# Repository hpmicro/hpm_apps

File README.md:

[中文](README_zh.md)

# HPM APPS introduction
HPM APPS is an upper layer application software development kit based on HPM SDK. It provides a variety of typical general-purpose application solutions, including middleware, components, services, etc., for users to use and evaluate.

## HPM APPS directory structure

| Directory name | Description |
|--------|--------|
| <HPM_APP_BASE>/boards | Files for various development boards |
| <HPM_APP_BASE>/components | Software components |
| <HPM_APP_BASE>/docs | Document |
| <HPM_APP_BASE>/middleware | Middleware |
| <HPM_APP_BASE>/apps | Samples of various solutions |
| <HPM_APP_BASE>/services | Software Services |
| <HPM_APP_BASE>/tools | Tool files |

## Instructions for using the HPM APP

### HPM SDK version requirements

Note: Each CASE of the HPM APP relies on the corresponding HPM SDK version. To ensure that the project can be built and compiled correctly, please refer to the SDK version dependency instructions in the README document located in the corresponding CASE directory.

### Build

Recommend using the sdk_env environment on Windows to build the SES compilation and debugging project. In the SDK ENV tool, check **Enable User Application Path** and select the **hpm_apps/apps** directory, or choose the demo directory you need. It is recommended to use the former, as it can scan all demo files.

If you want to add some middleware from hpm_apps/middleware, please add code in demo CMakeLists.txt, suggest you add code before `generate_ses_project`, for example:

```
add_subdirectory(../../.. hpm_apps/build_tmp)
generate_ses_project()
```

## HPM_APPS documentation

- Local document:
  The HPM_APPS document can be compiled locally, and after successful compilation, the local document can be accessed through the following portals:
  - <HPM_APP_BASE>>/docs/index.html
  - <HPM_APP_BASE>>/docs/index_zh.html

- Online documentation:
  - https://hpm-apps.readthedocs.io/en/latest/
  - https://hpm-apps.readthedocs.io/zh-cn/latest/

## Code repository
- hpm_apps github: https://github.com/hpmicro/hpm_apps
- hpm_sdk github: https://github.com/hpmicro/hpm_sdk
- sdk_env github: https://github.com/hpmicro/sdk_env
- sdk extra demo: https://github.com/hpmicro/hpm_sdk_extra
- openocd (hpmicro patched): https://github.com/hpmicro/riscv-openocd
- gnu gcc toolchain: https://github.com/hpmicro/riscv-gnu-toolchain

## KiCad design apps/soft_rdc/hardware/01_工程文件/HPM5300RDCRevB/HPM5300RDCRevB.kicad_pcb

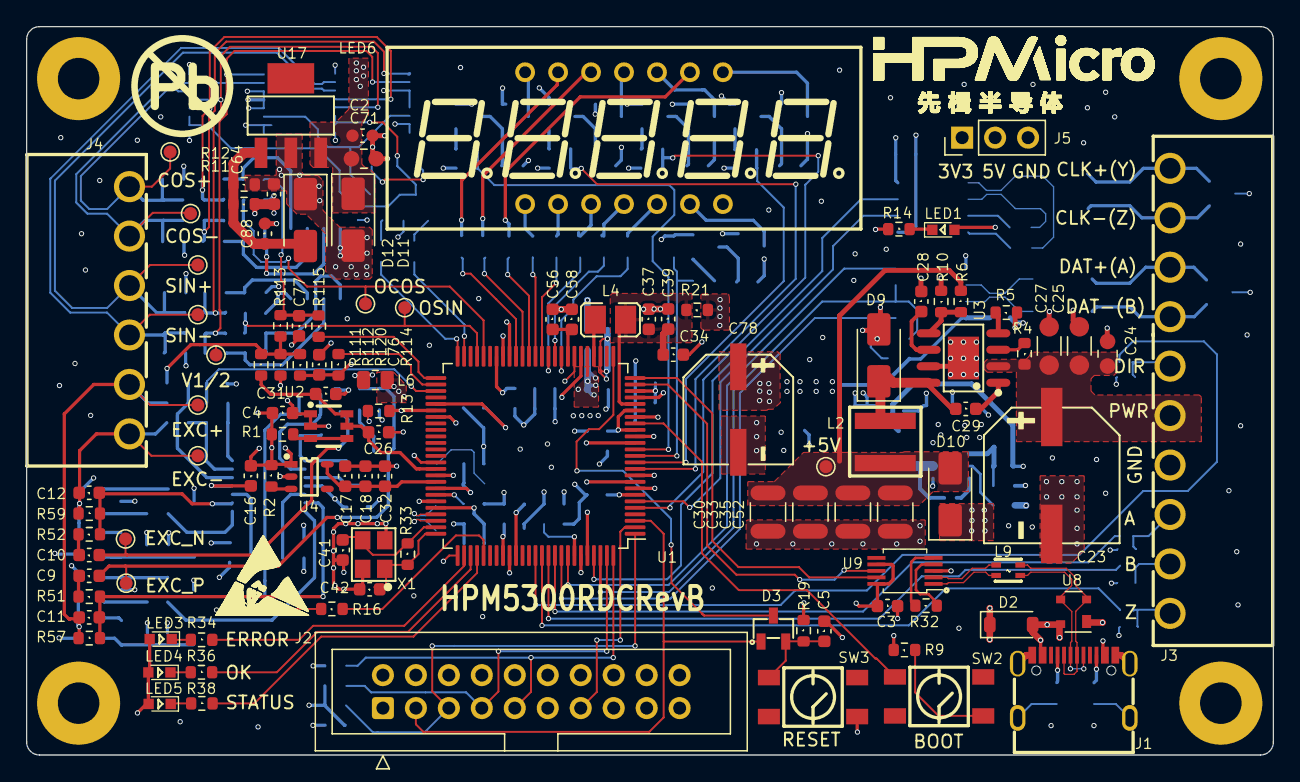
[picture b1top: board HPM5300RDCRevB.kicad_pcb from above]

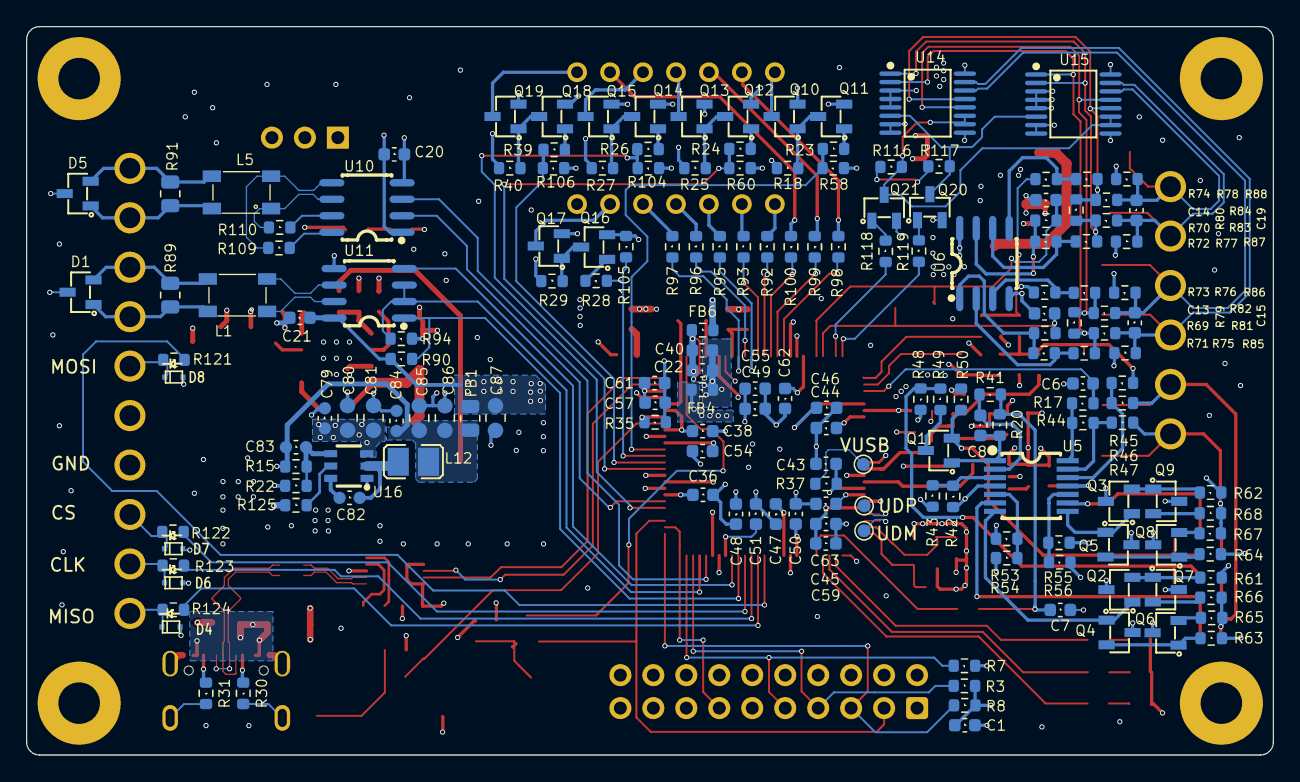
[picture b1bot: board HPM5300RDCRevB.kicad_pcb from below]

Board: 4 copper layers, 96.1 x 56.1 mm, 286 parts (173 on the bottom side), 181 nets.

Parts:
C1, C2, C3, C4, C5, C17, C20, C21, C22, C29, C31, C34, C36, C38, C43, C44, C45, C46, C47, C48, C49, C50, C51, C54, C56, C57, C58, C62, C63, C79, C82, C84: 0.1uF,50V; C_0603_1608Metric
C6, C13, C14: 15pF,50V; C_0603_1608Metric
C7: 4.7nF,50V; C_0603_1608Metric
C8: 1nF,50V; C_0603_1608Metric
C9, C10, C32, C76, C77: 10nF,50V; C_0603_1608Metric
C11, C12: 18pF,50V; C_0603_1608Metric
C15, C19: 1uF,50V; C_0603_1608Metric
C16, C18, C26, C88: 10uF,16V; C_0603_1608Metric
C23: 220uF,50V; CAP-SMD_BD10.0-L10.3-W10.3-FD
C24: 100pF; C_0805_2012Metric
C25, C27: 2.2uF,100V; C_1206_3216Metric
C28: 22nF,50V; C_0603_1608Metric
C30, C33, C35, C52: 47uF,16V,X7R; C_1210_3225Metric
C37, C39, C40: 22uF,10V; C_0603_1608Metric
C41, C42: 12pF,50V; C_0603_1608Metric
C55, C59: 10uF,10V; C_0603_1608Metric
C61: 4.7uF,16V; C_0603_1608Metric
C64: 1uF,25V; C_0603_1608Metric
C71, C80, C81, C85, C86, C87: 22uF,16V; C_0805_2012Metric
C78: 220uF,35V; CAP-SMD_BD8.0-L8.3-W8.3-LS9.1-FD
C83: 22pF,50V; C_0603_1608Metric
D1, D5: NUP2105L; SOT-23
D2: 1N5819HW-7-F; D_SOD-123
D3: BAT54A-7-F; SOT-23
D4, D6, D7, D8: D1213A-01T-7; SOD_523_1P4
D9, D10: SS1045; D_SMA
D11, D12: 1N4002; D_SMA
FB1: 100Ω@100MHz_2A; R_0805_2012Metric
FB4, FB6: 600Ω@100MHz_1.3A; R_0603_1608Metric
FID1, FID2, FID3, FID4: MountingHole_Pad; MountingHole_3.2mm_M3_Pad
J1: USB_Type-C; TYPE-C-16P
J2: 2.54-2*10P简牛; IDC-Header_2x10_P2.54mm
J3: Conn_01x10; CONN-TH_10P-P3.81_KF2EDGR-3.81-10P
J4: Conn_01x06; CONN-TH_6P-P3.81_KF2EDGR-3.81-6P
J5: Conn_01x03; PinHeader_1x03_P2.54mm_Vertical
L1, L5: ACT45B-510-2P-TL003; L4532
L2: 8.2uH_6.1A; IND-SMD_L5.5-W5.3_FEXL0520A-1R0M
L4, L12: 4.7uH_1.4A; L1008
L6: BLM21AG121SN1D; R_0805_2012Metric
L9: DLW21SN900SQ2L; L2012
LED1, LED4: LED_GREEN; LED_0603
LED3: LED_RED; LED_0603
LED5: LED_BLUE; LED_0603
LED6: SLR0365CRA1BD/AFN-3651A; LED-SEG-TH_SLR0365CRA1BD-AFN-3651A
Q1, Q2, Q3, Q6, Q8: BC817; SOT-23
Q4, Q5, Q7, Q9: BC807; SOT-23
Q10, Q13, Q15, Q17, Q19: IRLML6401; SOT-23
Q11, Q12, Q14, Q16, Q18, Q20, Q21: 2N7002; SOT-23
R1, R13, R81, R82, R83, R84: 0Ω; R_0603_1608Metric
R2, R3, R4, R7, R8, R9, R18, R19, R22, R25, R27, R29, R40, R44, R45, R48, R50, R53, R54, R55, R56, R58, R60, R71, R72, R73, R74, R90, R94, R104, R105, R106, R111, R112, R116, R117, R125: 10K; R_0603_1608Metric
R5: 84.5K; R_0603_1608Metric
R6, R46, R47, R51, R52, R79, R80, R85, R87: 100K; R_0603_1608Metric
R10: 17.8K; R_0603_1608Metric
R11: 3.6K; R_0603_1608Metric
R12: 240Ω; R_0603_1608Metric
R14, R23, R24, R26, R28, R34, R35, R36, R38, R39, R118, R119: 1K; R_0603_1608Metric
R15: 33.2K; R_0603_1608Metric
R16, R20: 3.9K; R_0603_1608Metric
R17, R37, R65, R66, R67, R68, R69, R70: 10Ω; R_0603_1608Metric
R21, R109, R110, R113, R120: 0Ω_0603; R_0603_1608Metric
R30, R31: 5.1K; R_0603_1608Metric
R32: 2K; R_0603_1608Metric
R33: 1M; R_0603_1608Metric
R41: 6.8K; R_0603_1608Metric
R42: 12K; R_0603_1608Metric
R43: 3K; R_0603_1608Metric
R49: 20Ω; R_0603_1608Metric
R57, R59: 470K; R_0603_1608Metric
R61, R62, R63, R64: 4.7K; R_0603_1608Metric
R75, R76, R77, R78: 3.3K; R_0603_1608Metric
R86, R88: 62K; R_0603_1608Metric
R89, R91: 120Ω; R_0805_2012Metric
R92, R93, R95, R96, R97, R98, R99, R100: 330Ω; R_0603_1608Metric
R114, R115: 36Ω; R_0603_1608Metric
R121, R122, R123, R124: 33Ω; R_0603_1608Metric
Ref**: Val**; ESD
SW2, SW3: 轻触开关4.5mm*4.5mm*4mm; 轻触开关SMD-4P,4.5x4.5mm
T1: EXC_N; TestPoint_Pad_D1.0mm
T2: EXC_P; TestPoint_Pad_D1.0mm
T3: EXC+; TestPoint_Pad_D1.0mm
T4: EXC-; TestPoint_Pad_D1.0mm
T5: V1/2; TestPoint_Pad_D1.0mm
T6: COS-; TestPoint_Pad_D1.0mm
T7: COS+; TestPoint_Pad_D1.0mm
T8: SIN-; TestPoint_Pad_D1.0mm
T9: SIN+; TestPoint_Pad_D1.0mm
T10: OCOS; TestPoint_Pad_D1.0mm
T11: OSIN; TestPoint_Pad_D1.0mm
TP1: VUSB; TestPoint_Pad_D1.0mm
TP2: UDP; TestPoint_Pad_D1.0mm
TP3: UDM; TestPoint_Pad_D1.0mm
TP4: 1.0mm; TestPoint_Pad_D1.0mm
U1: HPM5361ICB1; LQFP-100_14x14mm_P0.5mm
U2: REF3433IDBVR; SOT-23-6
U3: LMR14050SDDAR; SOIC-8EP
U4: TPS7A2033PDBVR; SOT-23-5
U5: TLV4171IPWR; TSSOP-14
U6: TLV2171IDR; SOIC-8
U8: PRTR5V0U2X; SOT-143
U9: CH340E; MSOP-10
U10: SIT3490EESA; SOIC-8
U11: MAX3485EESA+T; SOIC-8
U14, U15: CD4053BPWRG3; TSSOP-16_L5.0-W4.4-P0.65-LS6.4-BL
U16: TPS563201DDCR; SOT-23-6
U17: LM317T; SOT-223-3_L6.7-W3.7-P2.30-LS7.0-BR
X1: 24MHz ±10ppm 12pF; 3225

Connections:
+3.3V: C1.1, C3.1, C20.1, C21.1, C45.1, C46.1, C47.1, C48.1, C49.2, C54.1, C55.1, C59.1, C78.1, C87.1, FB1.1, FB4.2, J2.1 (VTREF), J5.1, LED3.2 (A), LED4.2 (A), LED5.2 (A), Q10.2 (S), Q13.2 (S), Q15.2 (S), Q17.2 (S), Q19.2 (S), R3.2, R8.2, R9.2, R18.1, R19.2, R25.1, R27.1, R29.1, R40.1, R90.2, U1.9 (VIO_B00), U1.15 (VIO_B00), U1.31 (VPMC), U1.42 (VIO_B01), U1.55 (VIO_B01), U1.71 (VPLL), U1.85 (VIO_B00), U1.96 (VIO_B00), U9.7 (VCC), U9.10 (V3), U10.1 (VCC), U11.8 (VCC)
+3.3VA: C17.1, C18.1, C32.1, U1.67 (VANA), U4.5 (OUT)
+5V: C79.1, C80.1, C81.1, D2.1 (K), D10.1 (K), J5.2, L6.1, LED1.2 (A), R125.1, U16.3 (VIN)
+5VD: D2.2 (A), J1.A4 (VBUS), J1.A9 (VBUS), J1.B4 (VBUS), J1.B9 (VBUS), U8.4 (VCC)
/HPM5300RDC MAINENTRY/02-HPM5300_MISC/USB0_N: TP3.1, U1.73 (USB_DM)
/HPM5300RDC MAINENTRY/02-HPM5300_MISC/USB0_P: TP2.1, U1.72 (USB_DP)
/HPM5300RDC MAINENTRY/03-HPM5300_IO/BOOT1: SW2.4, U1.18 (PA03/TMR1.CAPT1/URT0.CTS/I2C0.SDA/SPI3.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)
/HPM5300RDC MAINENTRY/03-HPM5300_IO/DAC0: C76.1, R73.2, R114.1, R120.2
/HPM5300RDC MAINENTRY/03-HPM5300_IO/DAC1: C77.1, R74.2, R113.2, R115.1
/HPM5300RDC MAINENTRY/03-HPM5300_IO/JTAG_TCK: J2.9 (TCK/SWDCLK), R7.2, U1.100 (PA06/TMR0.CAPT0/URT1.RXD/I2C1.SDA/SPI0.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)
/HPM5300RDC MAINENTRY/03-HPM5300_IO/JTAG_TDI: J2.5 (TDI), R8.1, U1.1 (PA05/TMR1.COMP2/URT1.DE/URT1.RTS/SPI0.S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)
/HPM5300RDC MAINENTRY/03-HPM5300_IO/JTAG_TDO: J2.13 (TDO/SWO), U1.2 (PA04/URT1.CTS/SPI0.CS0/CAN1.RXD/PWM0.P0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)
/HPM5300RDC MAINENTRY/03-HPM5300_IO/JTAG_TMS: J2.7 (TMS/SWDIO), R3.1, U1.99 (PA07/TMR0.COMP0/URT1.TXD/I2C1.SCL/SPI0.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)
/HPM5300RDC MAINENTRY/03-HPM5300_IO/JTAG_TRST: D3.1 (A), J2.3 (~TRST), U1.3 (PA08/TMR0.COMP1/URT2.TXD/I2C2.SCL/SPI3.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)
/HPM5300RDC MAINENTRY/03-HPM5300_IO/PA00: U1.25 (PA00/TMR1.COMP0/URT0.TXD/CAN0.TXD/PWM0.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), U9.9 (RXD)
/HPM5300RDC MAINENTRY/03-HPM5300_IO/PA01: U1.24 (PA01/TMR1.CAPT0/URT0.RXD/CAN0.RXD/PWM0.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), U9.8 (TXD)
/HPM5300RDC MAINENTRY/03-HPM5300_IO/PA10: R26.1, R104.2, U1.5 (PA10/TMR0.COMP2/URT2.DE/URT2.RTS/SPI3.C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)
/HPM5300RDC MAINENTRY/03-HPM5300_IO/PA11: U1.6 (PA11/URT2.CTS/SPI3.SCLK/PWM0.P7/PWM1.FA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), U10.2 (RO)
/HPM5300RDC MAINENTRY/03-HPM5300_IO/PA12: R24.1, R60.2, U1.11 (PA12/URT3.CTS/I2C3.SDA/SPI3.MISO/PWM0.P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)
/HPM5300RDC MAINENTRY/03-HPM5300_IO/PA13: R39.1, R106.2, U1.12 (PA13/TMR1.COMP3/URT3.DE/URT3.RTS/I2C3.S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)
/HPM5300RDC MAINENTRY/03-HPM5300_IO/PA14: R28.1, R105.2, U1.13 (PA14/URT3.RXD/SPI3.DAT2/CAN3.RXD/PWM0.P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)
/HPM5300RDC MAINENTRY/03-HPM5300_IO/PA15: R23.1, R58.2, U1.14 (PA15/TMR0.COMP3/URT3.TXD/SPI3.DAT3/CAN3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)
/HPM5300RDC MAINENTRY/03-HPM5300_IO/PA16: R94.2, U1.98 (PA16/TMR3.COMP0/URT4.TXD/CAN0.TXD/PWM0.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), U11.2 (~RE), U11.3 (DE)
/HPM5300RDC MAINENTRY/03-HPM5300_IO/PA17: U1.97 (PA17/TMR3.CAPT0/URT4.RXD/CAN0.RXD/PWM0.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), U10.3 (DI)
/HPM5300RDC MAINENTRY/03-HPM5300_IO/PA18: U1.93 (PA18/TMR3.COMP1/URT4.DE/URT4.RTS/I2C0.S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), U11.4 (DI)
/HPM5300RDC MAINENTRY/03-HPM5300_IO/PA19: R90.1, U1.92 (PA19/TMR3.CAPT1/URT4.CTS/I2C0.SDA/SPI1.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), U11.1 (RO)
/HPM5300RDC MAINENTRY/03-HPM5300_IO/PA20: R122.1, U1.91 (PA20/URT5.CTS/SPI2.CS0/CAN1.RXD/PWM0.FA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)
/HPM5300RDC MAINENTRY/03-HPM5300_IO/PA21: R123.1, U1.90 (PA21/TMR3.COMP2/URT5.DE/URT5.RTS/SPI2.S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)
/HPM5300RDC MAINENTRY/03-HPM5300_IO/PA22: R124.1, U1.89 (PA22/TMR2.CAPT0/URT5.RXD/I2C1.SDA/SPI2.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)
/HPM5300RDC MAINENTRY/03-HPM5300_IO/PA23: R121.1, U1.88 (PA23/TMR2.COMP0/URT5.TXD/I2C1.SCL/SPI2.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)
/HPM5300RDC MAINENTRY/03-HPM5300_IO/PA28: R16.1, U1.80 (PA28/URT7.CTS/I2C3.SDA/SPI1.MISO/XPI0.C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)
/HPM5300RDC MAINENTRY/03-HPM5300_IO/PA29: R38.2, U1.79 (PA29/TMR3.COMP3/URT7.DE/URT7.RTS/I2C3.S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)
/HPM5300RDC MAINENTRY/03-HPM5300_IO/PA30: R36.2, U1.78 (PA30/URT7.RXD/SPI1.DAT2/CAN3.RXD/XPI0.C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)
/HPM5300RDC MAINENTRY/03-HPM5300_IO/PA31: R34.2, U1.77 (PA31/TMR2.COMP3/URT7.TXD/SPI1.DAT3/CAN3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)
/HPM5300RDC MAINENTRY/03-HPM5300_IO/PB07: C6.1, R17.1, U1.53 (PB07/TMR0.COMP0/URT1.TXD/I2C1.SCL/SPI3.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)
/HPM5300RDC MAINENTRY/03-HPM5300_IO/PB08: R114.2, U1.52 (PB08/TMR0.COMP1/URT2.TXD/I2C2.SCL/SPI2.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)
/HPM5300RDC MAINENTRY/03-HPM5300_IO/PB09: R115.2, U1.51 (PB09/TMR0.CAPT1/URT2.RXD/I2C2.SDA/SPI2.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)
/HPM5300RDC MAINENTRY/03-HPM5300_IO/PB10: R119.1, U1.50 (PB10/TMR0.COMP2/URT2.DE/URT2.RTS/SPI2.C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)
/HPM5300RDC MAINENTRY/03-HPM5300_IO/PB11: R118.1, U1.49 (PB11/URT2.CTS/SPI2.SCLK/ACMP.COMP1/PWM1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)
/HPM5300RDC MAINENTRY/03-HPM5300_IO/PB13: C13.1, R69.2, T11.1, U1.47 (PB13/TMR1.COMP3/URT3.DE/URT3.RTS/I2C3.S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)
/HPM5300RDC MAINENTRY/03-HPM5300_IO/PB14: C14.1, R70.2, T10.1, U1.46 (PB14/URT3.RXD/SPI2.DAT2/CAN3.RXD/PWM0.F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)
/HPM5300RDC MAINENTRY/03-HPM5300_IO/PY00: R98.2, U1.41 (PY00/TMR3.COMP0/URT0.TXD/CAN2.TXD/PWM0.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)
/HPM5300RDC MAINENTRY/03-HPM5300_IO/PY01: R99.2, U1.40 (PY01/TMR3.CAPT0/URT0.RXD/CAN2.RXD/PWM0.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)
/HPM5300RDC MAINENTRY/03-HPM5300_IO/PY02: R100.2, U1.39 (PY02/TMR3.COMP1/URT0.DE/URT0.RTS/I2C2.S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)
/HPM5300RDC MAINENTRY/03-HPM5300_IO/PY03: R92.1, U1.38 (PY03/TMR3.CAPT1/URT0.CTS/I2C2.SDA/CAN3.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)
/HPM5300RDC MAINENTRY/03-HPM5300_IO/PY04: R93.1, U1.37 (PY04/URT1.CTS/SPI2.CS0/CAN3.RXD/PWM0.P4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)
/HPM5300RDC MAINENTRY/03-HPM5300_IO/PY05: R95.1, U1.36 (PY05/TMR3.COMP2/URT1.DE/URT1.RTS/SPI2.S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)
/HPM5300RDC MAINENTRY/03-HPM5300_IO/PY06: R96.1, U1.35 (PY06/TMR2.CAPT0/URT1.RXD/I2C3.SDA/SPI2.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)
/HPM5300RDC MAINENTRY/03-HPM5300_IO/PY07: R97.1, U1.34 (PY07/TMR2.COMP0/URT1.TXD/I2C3.SCL/SPI2.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)
/HPM5300RDC MAINENTRY/04-RDC_EXCT/EXC+: C11.2, J4.5, R46.2, R57.1, R65.1, R66.2, T3.1
/HPM5300RDC MAINENTRY/04-RDC_EXCT/EXC-: C12.2, J4.6, R47.2, R59.1, R67.1, R68.2, T4.1
/HPM5300RDC MAINENTRY/04-RDC_EXCT/EXC_N: C10.1, Q1.2 (E), R50.2, T1.1
/HPM5300RDC MAINENTRY/04-RDC_EXCT/EXC_P: C9.1, R48.1, R49.2, T2.1
/HPM5300RDC MAINENTRY/04-RDC_EXCT/VOPA: C64.1, D11.2 (A), D12.1 (K), Q2.3 (C), Q3.3 (C), Q6.3 (C), Q8.3 (C), R12.1, R42.2, R48.2, R53.2, R55.2, R63.2, R64.2, R85.1, R87.1, R116.1, R117.1, U5.4 (V+), U6.8 (VDD), U14.16 (VDD), U15.16 (VDD), U17.2 (OUT)
/HPM5300RDC MAINENTRY/05-RDC_SINCOS/COS+: C19.2, J4.1, R84.1, R88.1, T7.1, U15.14 (OUT/IN_AX_OR_AY)
/HPM5300RDC MAINENTRY/05-RDC_SINCOS/COS-: C19.1, J4.2, R83.1, R87.2, T6.1, U15.15 (OUT/IN_BX_OR_BY)
/HPM5300RDC MAINENTRY/05-RDC_SINCOS/CTRL_CMOS: Q21.3 (D), R116.2, U14.10 (B), U14.11 (A), U15.10 (B), U15.11 (A)
/HPM5300RDC MAINENTRY/05-RDC_SINCOS/ICOS+: R78.1, R80.2, R84.2, U14.13 (AY), U15.12 (AX)
/HPM5300RDC MAINENTRY/05-RDC_SINCOS/ICOS-: R77.1, R80.1, R83.2, U14.1 (BY), U15.2 (BX)
/HPM5300RDC MAINENTRY/05-RDC_SINCOS/INH_CMOS: Q20.3 (D), R117.2, U14.6 (INH), U15.6 (INH)
/HPM5300RDC MAINENTRY/05-RDC_SINCOS/ISIN+: R76.1, R79.2, R82.2, U14.12 (AX), U15.13 (AY)
/HPM5300RDC MAINENTRY/05-RDC_SINCOS/ISIN-: R75.1, R79.1, R81.2, U14.2 (BX), U15.1 (BY)
/HPM5300RDC MAINENTRY/05-RDC_SINCOS/SIN+: C15.2, J4.3, R82.1, R86.1, T9.1, U14.14 (OUT/IN_AX_OR_AY)
/HPM5300RDC MAINENTRY/05-RDC_SINCOS/SIN-: C15.1, J4.4, R81.1, R85.2, T8.1, U14.15 (OUT/IN_BX_OR_BY)
/HPM5300RDC MAINENTRY/06-DEBUGGER/DN1: J1.A7 (DN1), J1.B7 (DN2), L9.4, U8.2 (I/O1)
/HPM5300RDC MAINENTRY/06-DEBUGGER/DP1: J1.A6 (DP1), J1.B6 (DP2), L9.1, U8.3 (I/O2)
/HPM5300RDC MAINENTRY/06-DEBUGGER/UD+: L9.2, U9.1 (UD+)
/HPM5300RDC MAINENTRY/06-DEBUGGER/UD-: L9.3, U9.2 (UD-)
/HPM5300RDC MAINENTRY/07-MISC/CO_+: L5.2, R109.1, U10.5 (Y)
/HPM5300RDC MAINENTRY/07-MISC/CO_-: L5.1, R110.1, U10.6 (Z)
/HPM5300RDC MAINENTRY/07-MISC/DA_+: L1.2, U11.6 (A)
/HPM5300RDC MAINENTRY/07-MISC/DA_-: L1.1, U11.7 (B)
/HPM5300RDC MAINENTRY/07-MISC/DIG1_PWR: LED6.14 (DIG1), Q10.3 (D)
/HPM5300RDC MAINENTRY/07-MISC/DIG2_PWR: LED6.11 (DIG2), Q13.3 (D)
/HPM5300RDC MAINENTRY/07-MISC/DIG3_PWR: LED6.10 (DIG3), Q15.3 (D)
/HPM5300RDC MAINENTRY/07-MISC/DIG4_PWR: LED6.6 (DIG4), Q17.3 (D)
/HPM5300RDC MAINENTRY/07-MISC/DIG5_PWR: LED6.8 (DIG5), Q19.3 (D)
/HPM5300RDC MAINENTRY/07-MISC/SEI_CLK_OUT_N: D5.1 (K), J3.9, L5.4, R91.2
/HPM5300RDC MAINENTRY/07-MISC/SEI_CLK_OUT_P: D5.2 (K), J3.10, L5.3, R91.1
/HPM5300RDC MAINENTRY/07-MISC/SEI_DATA_N: D1.1 (K), J3.7, L1.4, R89.1
/HPM5300RDC MAINENTRY/07-MISC/SEI_DATA_P: D1.2 (K), J3.8, L1.3, R89.2
/HPM5300RDC MAINENTRY/RESETN: D3.3 (K), U1.26 (RESETN)
/HPM5300RDC MAINENTRY/VREF1/2: R45.1, R111.2, R112.1, R113.1, R120.1, T5.1
DCDC_GND: C22.2, C40.2, FB6.1, U1.28 (DCDC_GND)
DCDC_IN: C22.1, C40.1, FB4.1, U1.30 (DCDC_IN)
DCDC_LP: L4.2, U1.29 (DCDC_LP)
DCDC_SNS: C34.1, C37.1, C39.1, L4.1, R21.2, U1.21 (DCDC_SNS)
GND: C1.2, C3.2, C5.2, C20.2, C21.2, C23.2, C24.2, C25.2, C27.2, C28.2, C30.2, C33.2, C34.2, C35.2, C36.2, C37.2, C38.2, C39.2, C41.2, C42.2, C43.2, C44.2, C45.2, C46.2, C47.2, C48.2, C49.1, C50.2, C51.2, C52.2, C54.2, C55.2, C56.2, C57.2, C58.2, C59.2, C61.2, C62.2, C63.2, C78.2, C79.2, C80.2, C81.2, C84.2, C85.2, C86.2, C87.2, D1.3 (A), D4.2, D5.3 (A), D6.2, D7.2, D8.2, D9.2 (A), FB6.2, FID2.1, FID3.1, FID4.1, J1.1 (EP), J1.2 (EP), J1.3 (EP), J1.4 (EP), J1.A1 (GND), J1.A12 (GND), J1.B1 (GND), J1.B12 (GND), J2.4 (GND), J2.6 (GND), J2.8 (GND), J2.10 (GND), J2.12 (GND), J2.14 (GND), J2.16 (GND), J2.18 (GND), J2.20 (GND), J3.4, J5.3, Q11.2 (S), Q12.2 (S), Q14.2 (S), Q16.2 (S), Q18.2 (S), R5.1, R7.1, R10.1, R13.1, R14.1, R22.1, R30.2, R31.2, R35.1, R58.1, R60.1, R94.1, R104.1, R105.1, R106.1, SW3.2, U1.8 (VSS), U1.10 (VSS), U1.16 (VSS), U1.22 (VSS), U1.32 (VSS), U1.43 (VSS), U1.56 (VSS), U1.66 (VSS), U1.70 (VSS), U1.76 (VSS), U1.84 (VSS), U1.95 (VSS), U3.7 (GND), U3.9 (EP), U8.1 (GND), U9.3 (GND), U10.4 (GND), U11.5 (GND), U16.1 (GND), X1.2 (GND), X1.4 (GND)
GNDA: C2.2, C4.2, C6.2, C7.2, C13.2, C14.2, C16.2, C17.2, C18.2, C26.2, C31.2, C32.2, C64.2, C71.2, C76.2, C77.2, C88.2, Q4.3 (C), Q5.3 (C), Q7.3 (C), Q9.3 (C), Q20.2 (S), Q21.2 (S), R11.1, R13.2, R43.1, R50.1, R54.1, R56.1, R61.1, R62.1, R86.2, R88.2, R112.2, U1.64 (VREFL), U2.1 (GND_F), U2.2 (GND_S), U4.2 (GND), U5.11 (V-), U6.4 (VSS), U14.3 (CY), U14.4 (OUT/IN_CX_OR_CY), U14.5 (IN/OUT_CX), U14.7 (VEE), U14.8 (VSS), U14.9 (C), U15.3 (CY), U15.4 (OUT/IN_CX_OR_CY), U15.5 (IN/OUT_CX), U15.7 (VEE), U15.8 (VSS), U15.9 (C)
unnamed: C5.1, D3.2 (A), R19.1, SW3.4
unnamed: C7.1, R16.2, R20.1, R41.1
unnamed: C9.2, R51.2
unnamed: C10.2, R52.2
unnamed: C83.1, C84.1, C85.1, C86.1, FB1.2, L12.2, R15.2
unnamed: C29.1, D9.1 (K), L2.1, U3.8 (SW)
unnamed: C30.1, C33.1, C35.1, C52.1, D10.2 (A), L2.2, R6.2, TP4.1
unnamed: C88.1, D12.2 (A), R11.2, R12.2, U17.1 (ADJ)
unnamed: J1.A5 (CC1), R30.1
unnamed: J1.B5 (CC2), R31.1
unnamed: D4.1, J3.1, R124.2
unnamed: D6.1, J3.2, R123.2
unnamed: D7.1, J3.3, R122.2
unnamed: D8.1, J3.6, R121.2
unnamed: LED1.1 (K), R14.2
unnamed: LED3.1 (K), R34.1
unnamed: LED4.1 (K), R36.1
unnamed: LED5.1 (K), R38.1
unnamed: LED6.13 (A), R98.1
unnamed: LED6.9 (B), R100.1
unnamed: LED6.4 (C), R96.2
unnamed: LED6.2 (D), R93.2
unnamed: LED6.3 (DP), R95.2
unnamed: LED6.1 (E), R92.2
unnamed: LED6.12 (F), R99.1
unnamed: LED6.5 (G), R97.2
unnamed: C8.1, Q1.1 (B), R20.2, U5.1 (OUTA)
unnamed: Q1.3 (C), R49.1
unnamed: Q2.1 (B), Q4.1 (B), U5.7 (OUTB)
unnamed: Q2.2 (E), Q7.1 (B), R61.2
unnamed: Q3.1 (B), Q5.1 (B), U5.8 (OUTC)
unnamed: Q3.2 (E), Q9.1 (B), R62.2
unnamed: Q4.2 (E), Q6.1 (B), R63.1
unnamed: Q5.2 (E), Q8.1 (B), R64.1
unnamed: Q6.2 (E), R65.2
unnamed: Q7.2 (E), R66.1
unnamed: Q8.2 (E), R67.2
unnamed: Q9.2 (E), R68.1
unnamed: Q10.1 (G), Q11.3 (D), R18.2
unnamed: Q11.1 (G), R23.2
unnamed: Q12.3 (D), Q13.1 (G), R25.2
unnamed: Q12.1 (G), R24.2
unnamed: Q14.3 (D), Q15.1 (G), R27.2
unnamed: Q14.1 (G), R26.2
unnamed: Q16.3 (D), Q17.1 (G), R29.2
unnamed: Q16.1 (G), R28.2
unnamed: Q18.3 (D), Q19.1 (G), R40.2
unnamed: Q18.1 (G), R39.2
unnamed: Q20.1 (G), R119.2
unnamed: Q21.1 (G), R118.2
unnamed: R9.1, SW2.2
unnamed: R37.1, TP1.1
unnamed: C43.1, R37.2, U1.68 (USBVBUS)
unnamed: C41.1, R33.2, U1.74 (XTALI), X1.3 (X2)
unnamed: C42.1, R33.1, U1.75 (XTALO), X1.1 (X1)
unnamed: C57.1, C61.1, U1.23 (VDD_OTPCAP)
unnamed: C56.1, C58.1, U1.33 (VDD_PMCCAP)
unnamed: R35.2, U1.19 (PA02/TMR1.COMP1/URT0.DE/URT0.RTS/I2C0.S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)
unnamed: R1.2, U2.3 (ENABLE), U2.4 (IN)
unnamed: C29.2, U3.1 (BOOT)
unnamed: R4.1, U3.3 (EN)
unnamed: R6.1, R10.2, U3.5 (FB)
unnamed: R5.2, U3.4 (RT/SYNC)
unnamed: C28.1, U3.6 (SS)
unnamed: R2.1, U4.3 (EN)
unnamed: C4.1, C16.1, L6.2, R1.1, R2.2, U4.1 (IN)
unnamed: R42.1, R43.2, U5.3 (INA+)
unnamed: C8.2, R41.2, U5.2 (INA-)
unnamed: R53.1, R54.2, U5.5 (INB+)
unnamed: C11.1, R51.1, R57.2, U5.6 (INB-)
unnamed: R55.1, R56.2, U5.10 (INC+)
unnamed: C12.1, R52.1, R59.2, U5.9 (INC-)
unnamed: R45.2, R46.1, U5.12 (IND+)
unnamed: R44.2, R47.1, U5.13 (IND-)
unnamed: R17.2, R44.1, U5.14 (OUTD)
unnamed: R73.1, R76.2, U6.3 (VINA+)
unnamed: R71.1, R75.2, U6.2 (VINA-)
unnamed: R69.1, R71.2, U6.1 (VOUTA)
unnamed: R74.1, R78.2, U6.5 (VINB+)
unnamed: R72.1, R77.2, U6.6 (VINB-)
unnamed: R70.1, R72.2, U6.7 (VOUTB)
unnamed: R32.2, U9.5 (~CTS)
unnamed: R32.1, U9.4 (~RTS)
unnamed: R109.2, U10.8 (A)
unnamed: R110.2, U10.7 (B)
unnamed: R125.2, U16.5 (EN)
unnamed: C82.2, L12.1, U16.2 (SW)
unnamed: C82.1, U16.6 (VBST)
unnamed: C83.2, R15.1, R22.2, U16.4 (VFB)
VCC: C2.1, C23.1, C24.1, C25.1, C27.1, C71.1, D11.1 (K), J3.5, R4.2, U3.2 (VIN), U17.3 (IN)
VDD_SOC: C36.1, C38.1, C44.1, C50.1, C51.1, C62.1, C63.1, R21.1, U1.7 (VDD_SOC), U1.17 (VDD_SOC), U1.20 (VDD_SOC), U1.44 (VDD_SOC), U1.57 (VDD_SOC), U1.69 (VDD_SOC), U1.83 (VDD_SOC), U1.94 (VDD_SOC)
VREF_3.3V: C26.1, C31.1, R111.1, U1.65 (VREFH), U2.5 (OUT_S), U2.6 (OUT_F)

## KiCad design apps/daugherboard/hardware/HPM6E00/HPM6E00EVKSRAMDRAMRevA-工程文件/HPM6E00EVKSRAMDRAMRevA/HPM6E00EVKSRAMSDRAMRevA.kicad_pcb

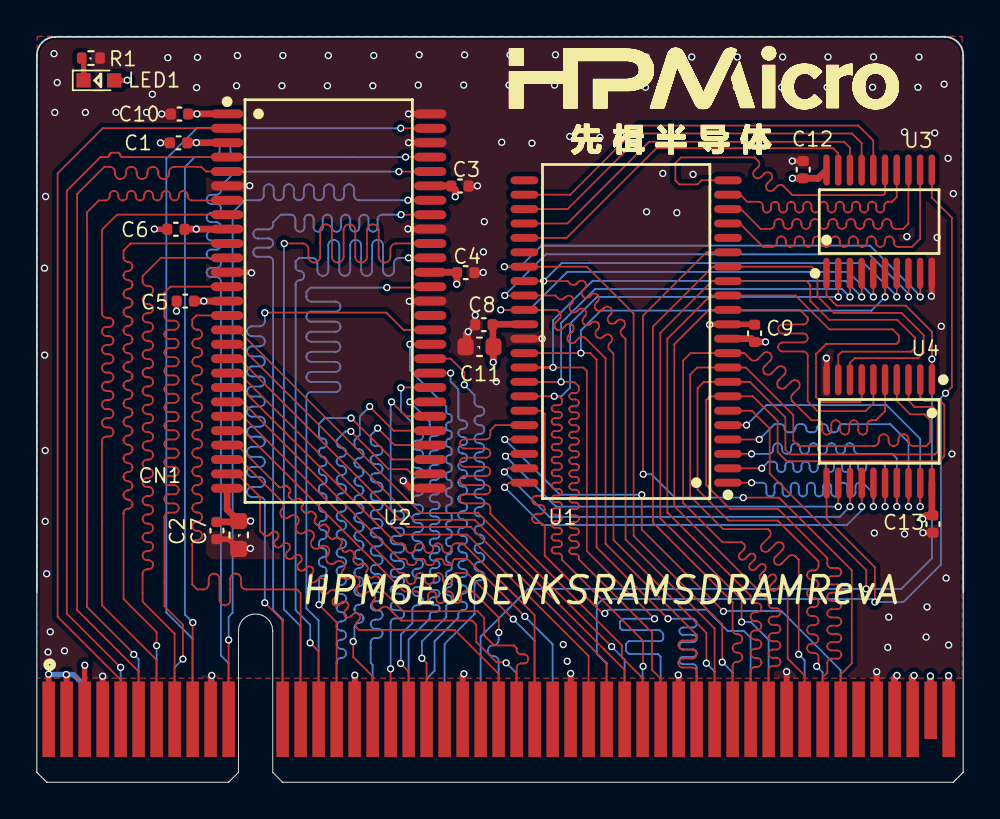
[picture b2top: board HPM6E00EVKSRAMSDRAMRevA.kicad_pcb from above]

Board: 4 copper layers, 51.5 x 41.4 mm, 20 parts (0 on the bottom side), 81 nets.

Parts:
C1, C2, C3, C4, C5, C6, C8, C9, C10, C12, C13: 0.1uF,16V; C_0402_1005Metric
C7, C11: 10uF,16V; C_0603_1608Metric
CN1: 3113-112T; 3113-112T 金手指2
LED1: LED_GREEN; LED_0603
R1: 2K; R_0402_1005Metric
U1: IS61WV12816DBLL-10TLI; TSOP-44_L18.4-W10.2-P0.80-LS11.8-BL
U2: W9825G6KH; TSOP-54-P0.8
U3, U4: SN74HC573APWR; TSSOP-20

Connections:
+3.3V: C1.1, C2.1, C3.1, C4.1, C5.1, C6.1, C7.1, C8.1, C9.1, C10.1, C11.1, C12.1, C13.1, CN1.A46, CN1.A47, CN1.A48, CN1.A49, CN1.B3, CN1.B46, CN1.B47, CN1.B48, CN1.B49, LED1.2 (A), U1.11 (VDD), U1.33 (VDD), U2.1 (VDD), U2.3 (VDDQ), U2.9 (VDDQ), U2.14 (VDD), U2.27 (VDD), U2.43 (VDDQ), U2.49 (VDDQ), U3.20 (VCC), U4.20 (VCC)
+5V: CN1.A1, CN1.A2, CN1.A3, CN1.B1, CN1.B2
/CTR0: CN1.B43, U1.17 (#WE)
/CTR1: CN1.A43, U1.41 (#OE)
/PC0: CN1.B8, U2.11 (DQ6)
/PC1: CN1.A8, U2.13 (DQ7)
/PC2: CN1.B9, U2.51 (DQ14)
/PC3: CN1.B7, U2.8 (DQ4)
/PC4: CN1.A7, U2.10 (DQ5)
/PC5: CN1.B6, U2.5 (DQ2)
/PC6: CN1.A6, U2.7 (DQ3)
/PC7: CN1.B5, U2.2 (DQ0)
/PC8: CN1.A5, U2.4 (DQ1)
/PC9: CN1.A9, U2.53 (DQ15)
/PC10: CN1.B11, U2.48 (DQ12)
/PC11: CN1.A11, U2.50 (DQ13)
/PC12: CN1.B12, U2.39 (UDQM)
/PC13: CN1.A12, U2.47 (DQ11)
/PC14: CN1.A13, U2.45 (DQ10)
/PC15: CN1.B13, U2.15 (LDQM)
/PC16: CN1.A14, U2.42 (DQ8)
/PC17: CN1.B14, U2.44 (DQ9)
/PC18: CN1.A15, U2.29 (A4)
/PC19: CN1.B15, U2.30 (A5)
/PC20: CN1.A17, U2.31 (A6)
/PC21: CN1.B17, U2.32 (A7)
/PC23: CN1.B18, U2.33 (A8)
/PC24: CN1.A19, U2.34 (A9)
/PC25: CN1.B19, U2.35 (A11)
/PC26: CN1.A20, U2.36 (A12)
/PC27: CN1.B20, U2.38 (CLK)
/PC28: CN1.A21, U2.37 (CKE)
/PC30: CN1.A23, U1.6 (#CE), U3.1 (OE#), U4.1 (OE#)
/PD0: CN1.A25, U2.25 (A2)
/PD1: CN1.B24, U2.26 (A3)
/PD2: CN1.A24, U2.23 (A0)
/PD3: CN1.B25, U2.24 (A1)
/PD4: CN1.A26, U2.22 (A10/AP)
/PD5: CN1.B26, U2.20 (BS0)
/PD6: CN1.A27, U2.21 (BS1)
/PD7: CN1.A30, U3.11 (LE), U4.11 (LE)
/PD10: CN1.B30, U2.18 (RAS#)
/PD11: CN1.B29, U2.19 (CS#)
/PD12: CN1.A31, U2.16 (WE#)
/PD13: CN1.B31, U2.17 (CAS#)
/PD14: CN1.A32, U1.38 (IO15), U3.2 (D0)
/PD15: CN1.B32, U1.40 (#UB)
/PD16: CN1.A33, U1.36 (IO13), U3.4 (D2)
/PD17: CN1.B33, U1.37 (IO14), U3.3 (D1)
/PD18: CN1.A35, U1.35 (IO12), U3.6 (D4)
/PD19: CN1.B35, U1.32 (IO11), U3.5 (D3)
/PD20: CN1.A36, U1.31 (IO10), U3.8 (D6)
/PD21: CN1.B36, U1.30 (IO9), U3.7 (D5)
/PD22: CN1.A37, U1.29 (IO8), U3.9 (D7)
/PD23: CN1.A38, U1.39 (#LB)
/PD24: CN1.B37, U1.16 (IO7), U4.8 (D6)
/PD25: CN1.A39, U1.15 (IO6), U4.9 (D7)
/PD26: CN1.B38, U1.14 (IO5), U4.7 (D5)
/PD27: CN1.B39, U1.13 (IO4), U4.6 (D4)
/PD28: CN1.B41, U1.10 (IO3), U4.5 (D3)
/PD29: CN1.A41, U1.9 (IO2), U4.4 (D2)
/PD30: CN1.A42, U1.8 (IO1), U4.3 (D1)
/PD31: CN1.B42, U1.7 (IO0), U4.2 (D0)
/SRAM/A0: U1.5 (A0), U4.19 (Q0)
/SRAM/A1: U1.4 (A1), U4.18 (Q1)
/SRAM/A2: U1.3 (A2), U4.17 (Q2)
/SRAM/A3: U1.2 (A3), U4.16 (Q3)
/SRAM/A4: U1.1 (A4), U4.15 (Q4)
/SRAM/A5: U1.44 (A5), U4.14 (Q5)
/SRAM/A6: U1.43 (A6), U4.13 (Q6)
/SRAM/A7: U1.42 (A7), U4.12 (Q7)
/SRAM/A8: U1.27 (A8), U3.19 (Q0)
/SRAM/A9: U1.26 (A9), U3.18 (Q1)
/SRAM/A10: U1.25 (A10), U3.17 (Q2)
/SRAM/A11: U1.24 (A11), U3.16 (Q3)
/SRAM/A12: U1.22 (A12), U3.15 (Q4)
/SRAM/A13: U1.21 (A13), U3.14 (Q5)
/SRAM/A14: U1.20 (A14), U3.13 (Q6)
/SRAM/A15: U1.19 (A15), U3.12 (Q7)
GND: C1.2, C2.2, C3.2, C4.2, C5.2, C6.2, C7.2, C8.2, C9.2, C10.2, C11.2, C12.2, C13.2, CN1.A4, CN1.A10, CN1.A16, CN1.A22, CN1.A28, CN1.A34, CN1.A40, CN1.A45, CN1.B4, CN1.B10, CN1.B16, CN1.B22, CN1.B28, CN1.B34, CN1.B40, CN1.B45, R1.1, U1.12 (GND), U1.34 (GND), U2.6 (VSSQ), U2.12 (VSSQ), U2.28 (VSS), U2.41 (VSS), U2.46 (VSSQ), U2.52 (VSSQ), U2.54 (VSS), U3.10 (GND), U4.10 (GND)
unnamed: LED1.1 (K), R1.2

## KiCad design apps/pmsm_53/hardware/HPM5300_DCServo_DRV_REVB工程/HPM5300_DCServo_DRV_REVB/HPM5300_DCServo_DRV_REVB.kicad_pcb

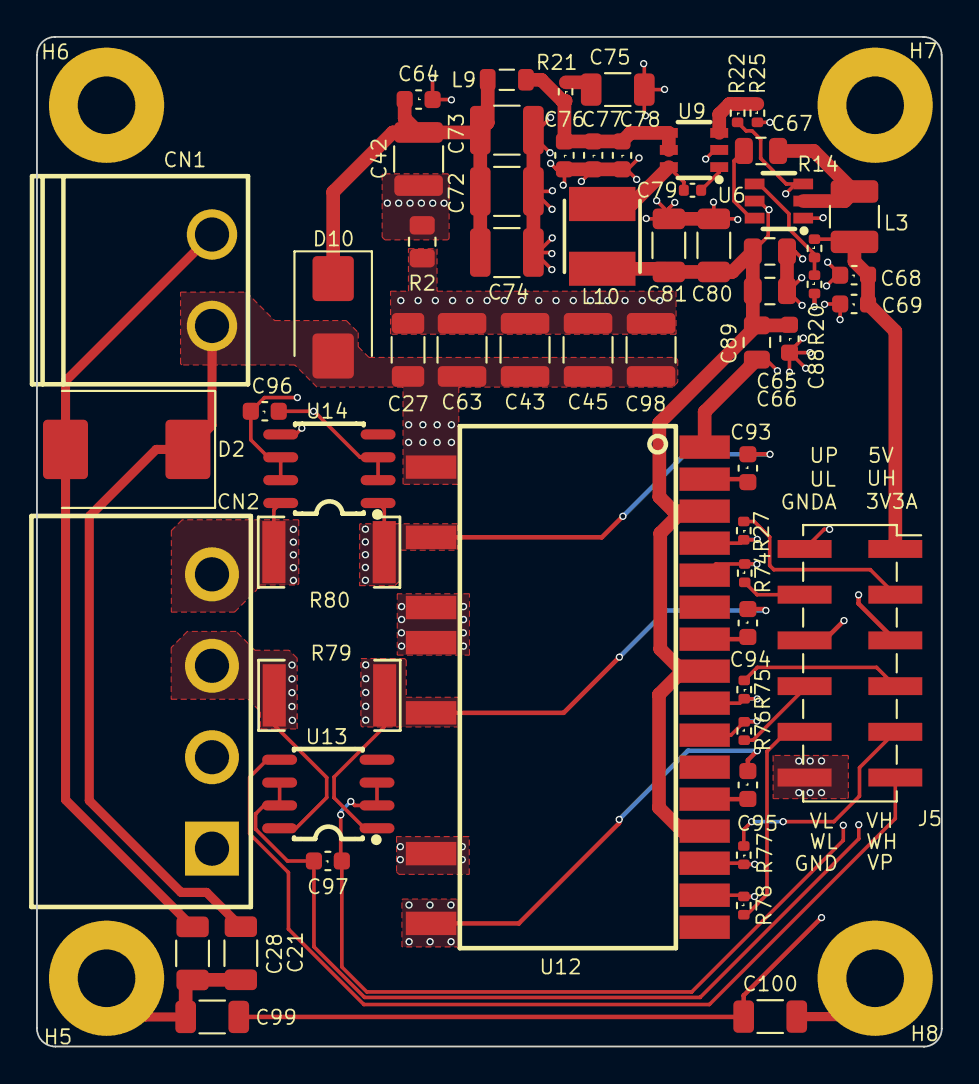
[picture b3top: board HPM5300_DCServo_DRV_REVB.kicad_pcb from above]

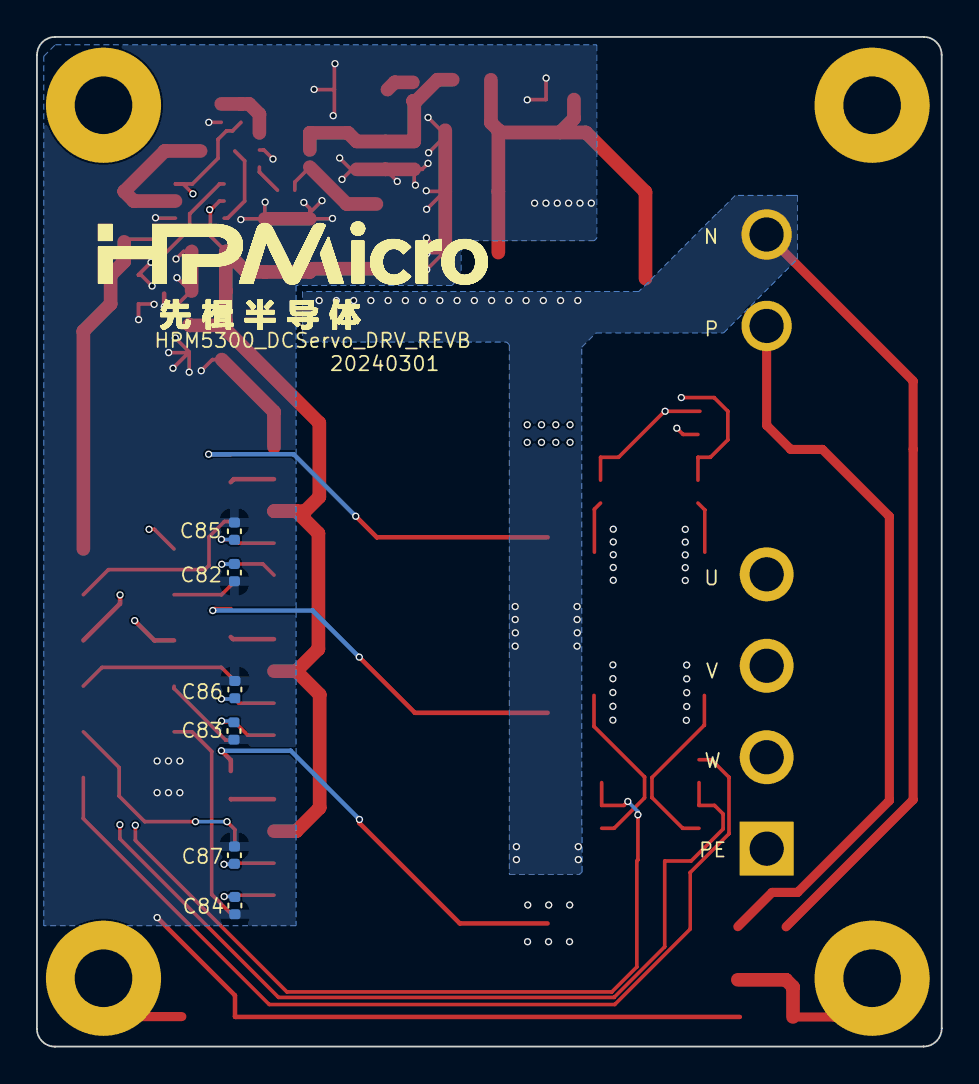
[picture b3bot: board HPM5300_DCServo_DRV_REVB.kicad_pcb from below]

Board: 4 copper layers, 50.3 x 56.1 mm, 70 parts (6 on the bottom side), 39 nets.

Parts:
C21, C27, C28, C99, C100: 10nF,630V,1206; C_1206_3216Metric
C42, C43, C45, C63, C72, C73, C74, C98: 10uF,63V; C_1210_3225Metric
C64, C88, C96, C97: 0.1uF,50V; C_0603_1608Metric
C65, C66, C89: 10uF,35V; C_0805_2012Metric
C67: 100nF,25V; C_0805_2012Metric
C68, C69: 22uF,10V; C_0603_1608Metric
C75: 4.7uF,50V; C_1206_3216Metric
C76, C77: 1uF,50V; C_0603_1608Metric
C78: 100nF,50V; C_0603_1608Metric
C79: 100nF,16V; C_0402_1005Metric
C80, C81: 10uF,50V; C_1206_3216Metric
C82, C83, C84, C85, C86, C87: 1nF,50V; C_0402_1005Metric
C93, C94, C95: 2.2uF,50V; C_0603_1608Metric
CN1: DB2ERC-5.08-2P; CONN-TH_2P-P5.08_DB2ERC-5.08-2P
CN2: DB2ERC-5.08-4P; CONN-TH_4P-P5.08_DB2ERC-5.08-4P
D2: SMDJ36CA_C350851; D_SMC
D10: 200V,2A; D_SMB
H5, H6, H7, H8: MountingHole_Pad; MountingHole_3.2mm_M3_Pad
J5: Conn_02x06; PinSocket_2x06_P2.54mm_Vertical_SMD
L3: 4.7uH_1.6A; L_1210_3225Metric
L9: 1.5uH; L_0805_2012Metric
L10: 22uH，1.3A; IND-SMD_L4.0-W4.0_SLW4010S
R2: 0Ω_0805; R_0805_2012Metric
R14: 56.2K; R_0402_1005Metric
R20: 10K; R_0402_1005Metric
R21: 1.58Ω; R_0402_1005Metric
R22: 309K; R_0402_1005Metric
R25: 22.1k; R_0402_1005Metric
R27, R74, R75, R76, R77, R78: 0Ω; R_0402_1005Metric
R79, R80: 10mΩ; R2512
U6: TPS562200DDCR; SOT-23-6_L2.9-W1.6-P0.95-LS2.8-BR
U9: LMR50410XDBVR; SOT-23-6
U12: SDM05M50DAS; SEMI_XNS50660ABS
U13, U14: INA240A1D; SOIC-8

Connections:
+3.3VA: C96.2, C97.2, J5.5, U13.6 (VS), U13.7 (REF1), U14.6 (VS), U14.7 (REF1)
+5V: C68.1, C69.1, J5.1, L3.2, R14.2
+15V: C65.1, C66.1, C80.1, C81.1, C88.1, C89.1, L10.2, R22.2, U6.3 (VIN), U6.5 (EN), U12.3 (VCC(U)), U12.8 (VCC(V)), U12.13 (VCC(W))
+24V: C42.1, C64.1, C72.1, C73.1, C74.1, D10.1 (K), L9.1
/MAIN/DRV/ADC0: J5.2, U14.5 (OUT)
/MAIN/DRV/ADC1: J5.11, U13.5 (OUT)
/MAIN/DRV/PWM_0: J5.3, R27.1
/MAIN/DRV/PWM_1: J5.4, R74.1
/MAIN/DRV/PWM_4: J5.7, R75.1
/MAIN/DRV/PWM_5: J5.8, R76.1
/MAIN/DRV/PWM_6: J5.9, R77.1
/MAIN/DRV/PWM_7: J5.10, R78.1
/MAIN/DRV/PWM_UH: C85.1, R27.2, U12.4 (IN(UH))
/MAIN/DRV/PWM_UL: C82.1, R74.2, U12.5 (IN(UL))
/MAIN/DRV/PWM_VH: C86.1, R75.2, U12.9 (IN(VH))
/MAIN/DRV/PWM_VL: C83.1, R76.2, U12.10 (IN(VL))
/MAIN/DRV/PWM_WH: C87.1, R77.2, U12.14 (IN(WH))
/MAIN/DRV/PWM_WL: C84.1, R78.2, U12.15 (IN(WL))
/MAIN/DRV/U+: CN2.4, R80.2, U14.8 (IN+)
/MAIN/DRV/U-: C93.2, R80.1, U12.18 (U_VS(U)), U14.1 (IN-)
/MAIN/DRV/V+: CN2.3, R79.2, U13.8 (IN+)
/MAIN/DRV/V-: C94.2, R79.1, U12.21 (V_VS(V)), U13.1 (IN-)
/MAIN/DRV/VBU: C93.1, U12.2 (VB(U))
/MAIN/DRV/VBV: C94.1, U12.7 (VB(V))
/MAIN/DRV/VBW: C95.1, U12.12 (VB(W))
/MAIN/DRV/W: C95.2, CN2.2, U12.23 (W_VS(W))
GND: C42.2, C64.2, C65.2, C66.2, C68.2, C69.2, C72.2, C73.2, C74.2, C75.2, C76.2, C77.2, C78.2, C80.2, C81.2, C82.2, C83.2, C84.2, C85.2, C86.2, C87.2, C88.2, C89.2, C99.1, C100.2, J5.12, R2.1, R20.1, R25.1, U6.1 (GND), U9.2 (GND), U12.1 (COM)
GNDA: C96.1, C97.1, J5.6, U13.2 (GND), U13.3 (REF2), U14.2 (GND), U14.3 (REF2)
N: C27.2, C28.1, C43.2, C45.2, C63.2, C98.2, CN1.1, D2.2 (A1), R2.2, U12.19 (NU), U12.20 (NV), U12.22 (NW)
unnamed: C75.1, R21.1
unnamed: C67.1, L3.1, U6.2 (SW)
unnamed: C67.2, U6.6 (VBST)
unnamed: R14.1, R20.2, U6.4 (VFB)
unnamed: C79.2, U9.1 (CB)
unnamed: C76.1, C77.1, C78.1, L9.2, R21.2, U9.4 (EN), U9.5 (VIN)
unnamed: R22.1, R25.2, U9.3 (FB)
unnamed: C79.1, L10.1, U9.6 (SW)
P: C21.2, C27.1, C43.1, C45.1, C63.1, C98.1, CN1.2, D2.1 (A2), D10.2 (A), U12.17
PE: C21.1, C28.2, C99.2, C100.1, CN2.1, H5.1, H8.1
